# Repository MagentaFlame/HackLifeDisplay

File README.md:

Week 4 Display - let's make something more useful loll
This means no LOL references (or will there???)
Update: no LOL references unfortunately... HLE got eliminated so I'm feeling down.

Schematics!

I added 8 pixels, initially for a "ring" but realized that microcontroller needed to plug in somewhere lol. Cool sequences could be done with this setup that I'll show in PCB. Anyways, added a switch to change color themes - sometimes cool tones are just not it - we need some warmth in life lol

PCB!

I made it in this weird fashion so the pixel lights running through would look cool and it will fit. I chose Hand Solder footprints so I can actually solder the 0603 stuff. I'm quite nervous for soldering!

Code!

Basically, it was a big learning curve, but through searching code libraries, tutorials, research, etc etc, I managed to do it. I call a Wifi client and HTTP client, using my free API key from OpenWeatherMap. HTTP client gets the info and puts into a Json doc, which I parse for the weather section's "main" weather condition and weather ID for more specifics. I then pass it into a function to update the colors based on the inputs (added a bunch of cool colors that hopefully will look good). I added millis so it would update every 30 min, so my api would work for the whole month with enough calls. 

CAD!(?)

https://cad.onshape.com/documents/576eb80d83ee613553f22006/w/4f6dd9364f57957917df3f42/e/1331975d95a1b04019fdb0a0 
So I wanted to make a bottom mount, then resin print the top container, but I ran out of time and budget. So, I'm just gonna get the hardware part fully done. I have the bottom mount done - if my school lets me I'll print it there. If not, it'll just be a simple add-on for the future!

BOM!

I'm a bit over... I'm super sorry but I cannot cut this down any further...

Hopefully I can get the solder from the shop!

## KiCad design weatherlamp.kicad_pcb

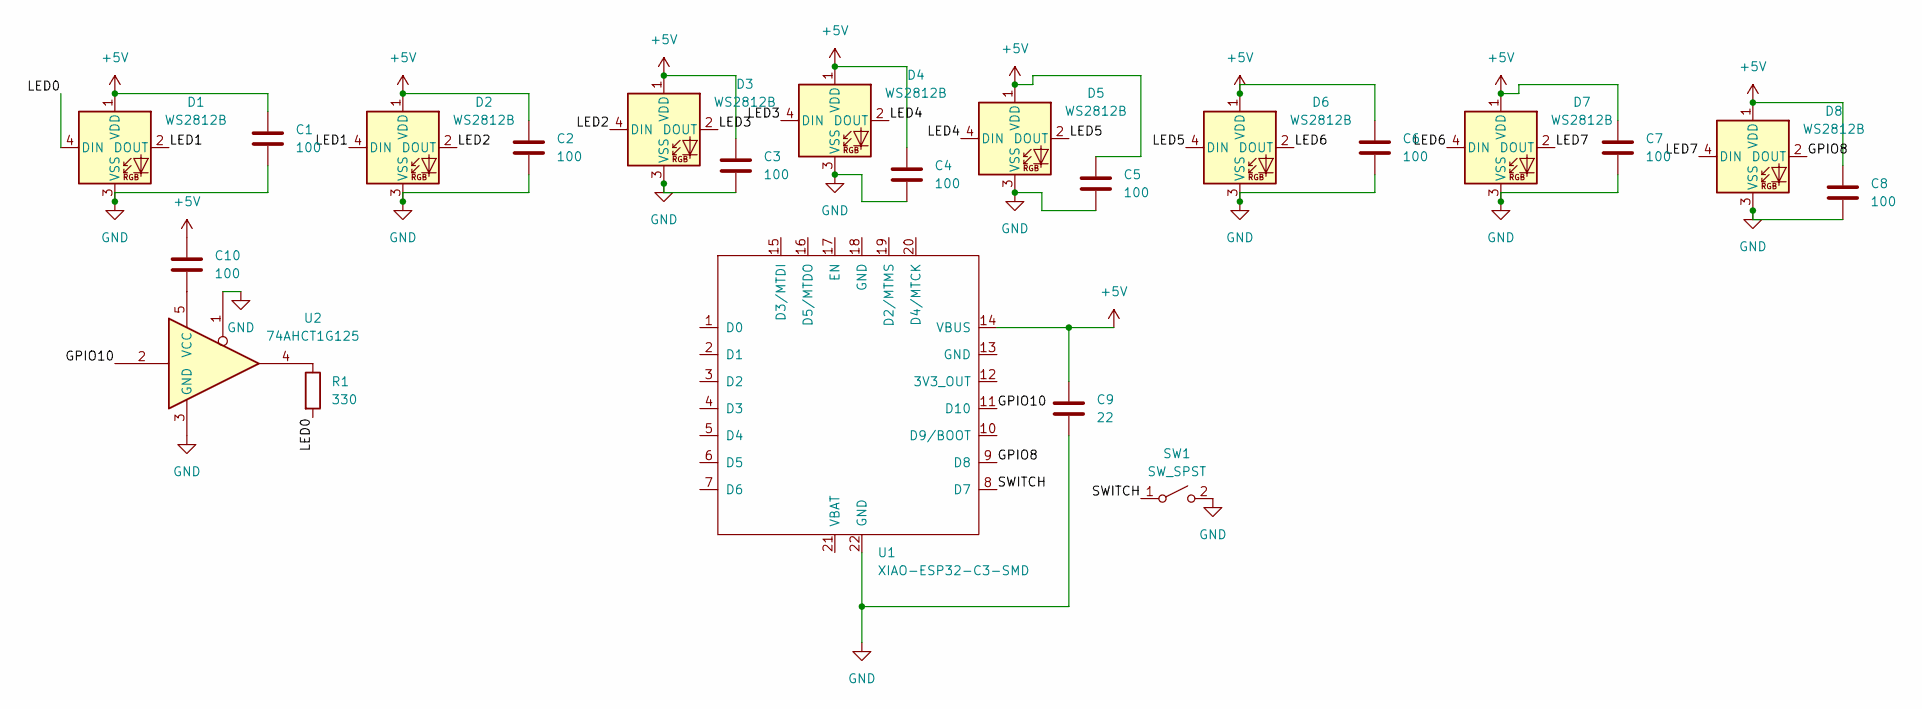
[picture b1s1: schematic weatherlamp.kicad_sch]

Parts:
C1, C2, C3, C4, C5, C6, C7, C8, C10: 100; C_0603_1608Metric_Pad1.08x0.95mm_HandSolder
C9: 22; C_1206_3216Metric_Pad1.33x1.80mm_HandSolder
D1, D2, D3, D4, D5, D6, D7, D8: WS2812B; LED_WS2812B_PLCC4_5.0x5.0mm_P3.2mm
R1: 330; R_0603_1608Metric_Pad0.98x0.95mm_HandSolder
SW1: SW_SPST; SW_DIP_SPSTx01_Slide_Copal_CHS-01A_W5.08mm_P1.27mm_JPin
U1: XIAO-ESP32-C3-SMD
U2: 74AHCT1G125; SOT-23-5_HandSoldering

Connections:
+5V: C1.1, C2.1, C3.1, C4.1, C5.1, C6.1, C7.1, C8.1, C9.1, C10.1, D1.1 (VDD), D2.1 (VDD), D3.1 (VDD), D4.1 (VDD), D5.1 (VDD), D6.1 (VDD), D7.1 (VDD), D8.1 (VDD), U1.14 (VBUS)
/GPIO8: D8.2 (DOUT), U1.9 (D8)
/GPIO10: U1.11 (D10), U2.2
/LED0: D1.4 (DIN), R1.2
/LED1: D1.2 (DOUT), D2.4 (DIN)
/LED2: D2.2 (DOUT), D3.4 (DIN)
/LED3: D3.2 (DOUT), D4.4 (DIN)
/LED4: D4.2 (DOUT), D5.4 (DIN)
/LED5: D5.2 (DOUT), D6.4 (DIN)
/LED6: D6.2 (DOUT), D7.4 (DIN)
/LED7: D7.2 (DOUT), D8.4 (DIN)
/SWITCH: SW1.1 (A), U1.8 (D7)
GND: C1.2, C2.2, C3.2, C4.2, C5.2, C6.2, C7.2, C8.2, C9.2, D1.3 (VSS), D2.3 (VSS), D3.3 (VSS), D4.3 (VSS), D5.3 (VSS), D6.3 (VSS), D7.3 (VSS), D8.3 (VSS), SW1.2 (B), U1.22 (GND), U2.1, U2.3 (GND)
unnamed: R1.1, U2.4
unnamed: C10.2, U2.5 (VCC)

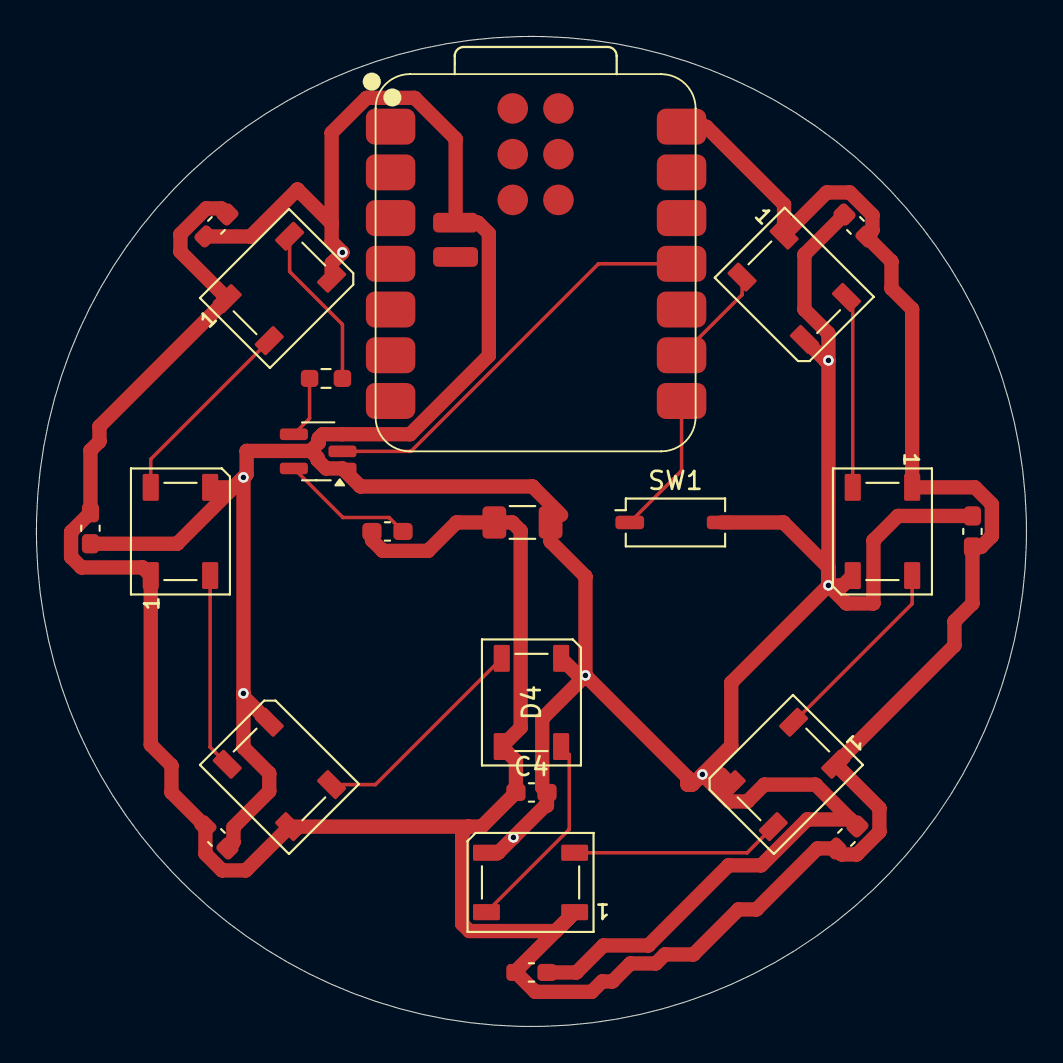
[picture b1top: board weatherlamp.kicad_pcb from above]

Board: 2 copper layers, 55.0 x 55.0 mm, 22 parts (0 on the bottom side), 15 nets.

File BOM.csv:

Item,Qty,Supplier,Cost/item,Total Cost,link
Custom PCB,1,JLCPCB,$3.12,$3.12,https://cart.jlcpcb.com/shopcart/cart/
LED WS2812B,1,Aliexpress,$1.38,$1.38,https://www.aliexpress.us/item/2255801159561004.html?spm=a2g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
ESP32 - C3,1,Aliexpress,$3.99,$3.99,https://www.aliexpress.us/item/3256810242798012.html?spm=a2g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
Capacitor 1206 22nf,1,Aliexpress,$4.33,$4.33,https://www.aliexpress.us/item/3256807340513507.html?spm=a2g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
Slide Switch SMD P1.27mm,1,Alibaba,$0.21,$0.21,https://www.alibaba.com/product-detail/Original-KE-DIP-Switc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
Resistor 300ohm 0603 1608,1,Aliexpress,$2.27,$2.27,https://aliexpress.us/item/3256813115149619.html?spm=a2g0o.c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
74AHCT1G125,1,Aliexpress,$5.85,$5.85,https://aliexpress.us/item/3256809059455719.html?spm=a2g0o.c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
Capacitor 0603 0.1uF,1,Aliexpress,$1.01,$1.01,https://aliexpress.com/item/3256808313403414.html?spm=a2g0o.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
Estimated total shipping,1,,,$8.11,
